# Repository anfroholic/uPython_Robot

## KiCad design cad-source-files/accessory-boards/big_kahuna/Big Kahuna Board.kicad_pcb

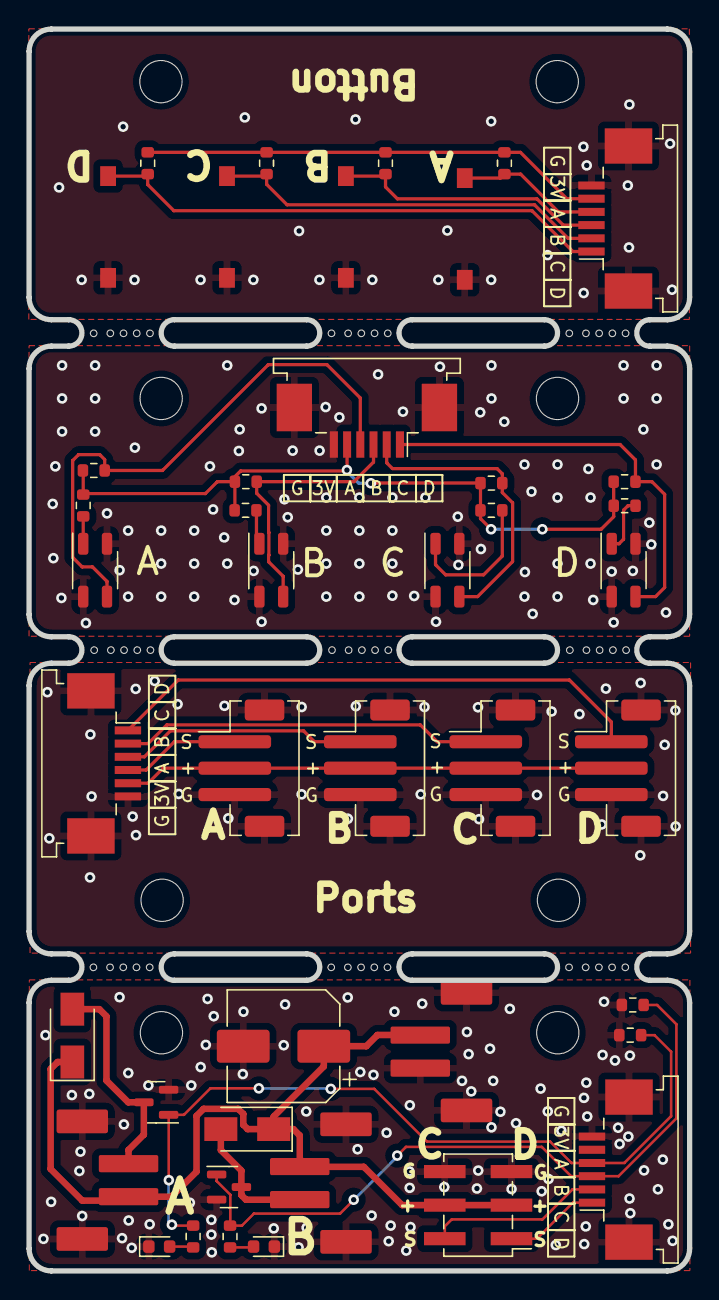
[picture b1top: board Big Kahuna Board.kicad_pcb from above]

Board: 2 copper layers, 50.0 x 94.0 mm, 51 parts (0 on the bottom side), 23 nets.

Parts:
C1: 220uF; CP_Elec_8x6.5
D1, D3: led_g; LED_0603_1608Metric
D2, D4: SX35_SCHOTTKY; D_SMA
H1, H1#2, H1#3, H1#4, H2, H2#2, H2#3, H2#4: MountingHole; MountingHole_3.2mm_M3_ISO14580
J1, J2, J6: Conn_01x02; JST_XH_2_VERTICAL
J2#2, J5, J7, J8: Conn_01x03; JST_PH_B3B-PH-SM4-TB_1x03-1MP_P2.00mm_Vertical
J4: Servo Header x2; PinHeader_2x03_P2.54mm_Vertical_SMD
J9, J9#2, J9#3, J9#4: Conn_01x06_MountingPin; TE_84952-6_1x06-1MP_P1.0mm_Horizontal
Q1, Q2: LOW PWR FET; SOT-23
R1, R2, R3#2, R4, R4#2, R7, R11, R14: 10k; R_0603_1608Metric
R3, R6, R9, R12: R100; R_0603_1608Metric
R5, R8, R10, R13: 10K; R_0603_1608Metric
SW1, SW2, SW3, SW4: SW_Push; SWITCH_2x3_SMD_TACTILE_GREEN
U1, U2, U3, U4: QRE1113GR; OnSemi_CASE100CY

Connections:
+3V3: J2#2.2, J5.2, J7.2, J8.2, J9.5, J9#2.5, J9#3.5, J9#4.5, R3.1, R4#2.2, R5.1, R6.1, R7.2, R8.1, R9.1, R10.1, R11.2, R12.1, R13.1, R14.2
+VDC: C1.1, D2.1 (K), D4.1 (K), J1.1, J2.1, J4.3, J4.4, J6.1
/A: J2#2.1, J9#4.1
/B: J5.1, J9#4.2
/Button A: J9#2.4, J9#3.1, R4#2.1, R13.2, SW1.1, U4.3
/Button B: J9#2.3, J9#3.2, R7.1, R10.2, SW2.1, U3.3
/Button C: J9#2.2, J9#3.3, R5.2, R11.1, SW3.1, U1.3
/Button D: J9#2.1, J9#3.4, R8.2, R14.1, SW4.1, U2.3
/C: J7.1, J9#4.3
/D: J8.1, J9#4.4
/SERVO_2: J4.2, J9.2
/SERVO_4: J4.1, J9.1
/Thing 1: J9.4, Q1.1 (G), R1.2, R2.2
/Thing 2: J9.3, Q2.1 (G), R3#2.2, R4.2
GND: C1.2, D1.1 (K), D3.1 (K), J1.MP (MountPin), J2.MP (MountPin), J2#2.3, J2#2.MP (MountPin), J4.5, J4.6, J5.3, J5.MP (MountPin), J6.2, J6.MP (MountPin), J7.3, J7.MP (MountPin), J8.3, J8.MP (MountPin), J9.6, J9.MP (MountPin), J9#2.6, J9#2.MP (MountPin), J9#3.6, J9#3.MP (MountPin), J9#4.6, J9#4.MP (MountPin), Q1.2 (S), Q2.2 (S), R2.1, R4.1, SW1.2, SW2.2, SW3.2, SW4.2, U1.2 (K), U1.4, U2.2 (K), U2.4, U3.2 (K), U3.4, U4.2 (K), U4.4
unnamed: D1.2 (A), R1.1
unnamed: D2.2 (A), J1.2, Q1.3 (D)
unnamed: D3.2 (A), R3#2.1
unnamed: D4.2 (A), J2.2, Q2.3 (D)
unnamed: R3.2, U1.1 (A)
unnamed: R6.2, U2.1 (A)
unnamed: R9.2, U3.1 (A)
unnamed: R12.2, U4.1 (A)

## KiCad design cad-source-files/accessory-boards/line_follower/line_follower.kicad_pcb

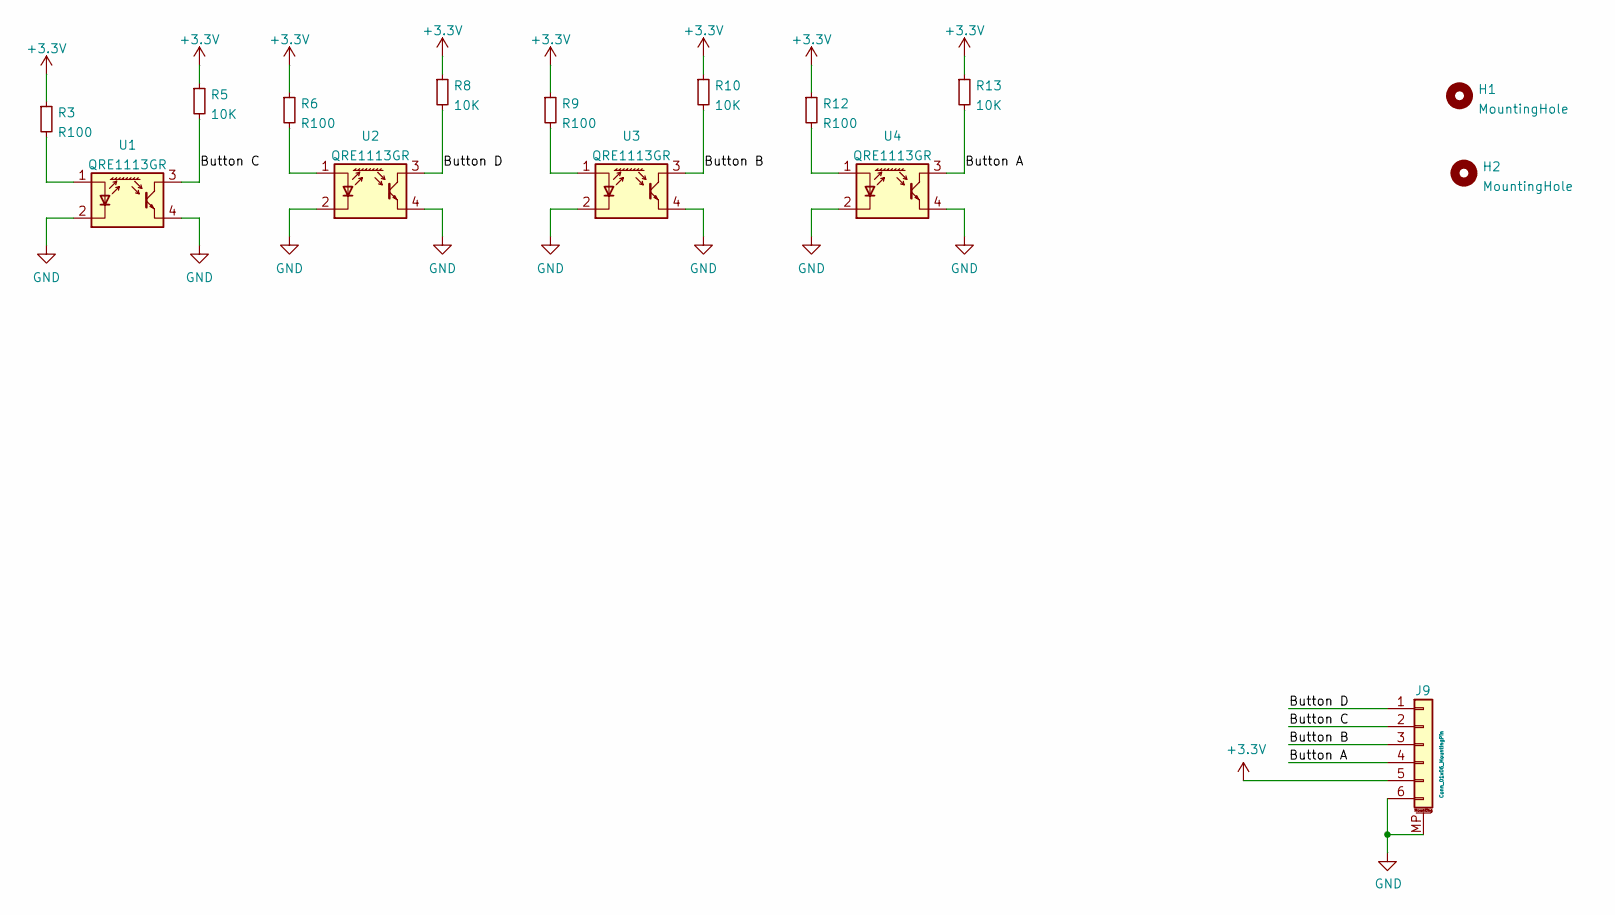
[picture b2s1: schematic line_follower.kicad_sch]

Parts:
H1, H2: MountingHole; MountingHole_3.2mm_M3_ISO14580
J9: Conn_01x06_MountingPin; TE_84952-6_1x06-1MP_P1.0mm_Horizontal
R3, R6, R9, R12: R100; R_0603_1608Metric
R5, R8, R10, R13: 10K; R_0603_1608Metric
U1, U2, U3, U4: QRE1113GR; OnSemi_CASE100CY

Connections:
+3V3: J9.5, R3.1, R5.1, R6.1, R8.1, R9.1, R10.1, R12.1, R13.1
/Button A: J9.4, R13.2, U4.3
/Button B: J9.3, R10.2, U3.3
/Button C: J9.2, R5.2, U1.3
/Button D: J9.1, R8.2, U2.3
GND: J9.6, J9.MP (MountPin), U1.2 (K), U1.4, U2.2 (K), U2.4, U3.2 (K), U3.4, U4.2 (K), U4.4
unnamed: R3.2, U1.1 (A)
unnamed: R6.2, U2.1 (A)
unnamed: R9.2, U3.1 (A)
unnamed: R12.2, U4.1 (A)

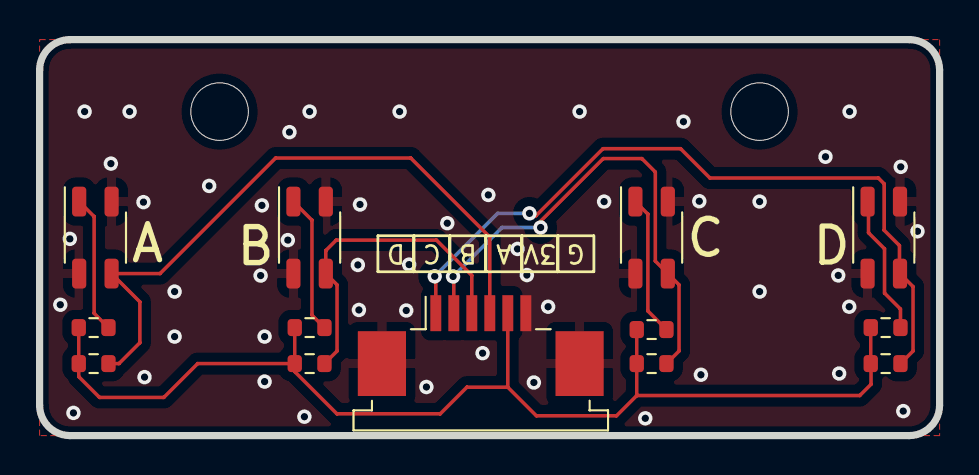
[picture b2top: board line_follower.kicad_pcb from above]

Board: 2 copper layers, 50.0 x 22.0 mm, 15 parts (0 on the bottom side), 10 nets.
